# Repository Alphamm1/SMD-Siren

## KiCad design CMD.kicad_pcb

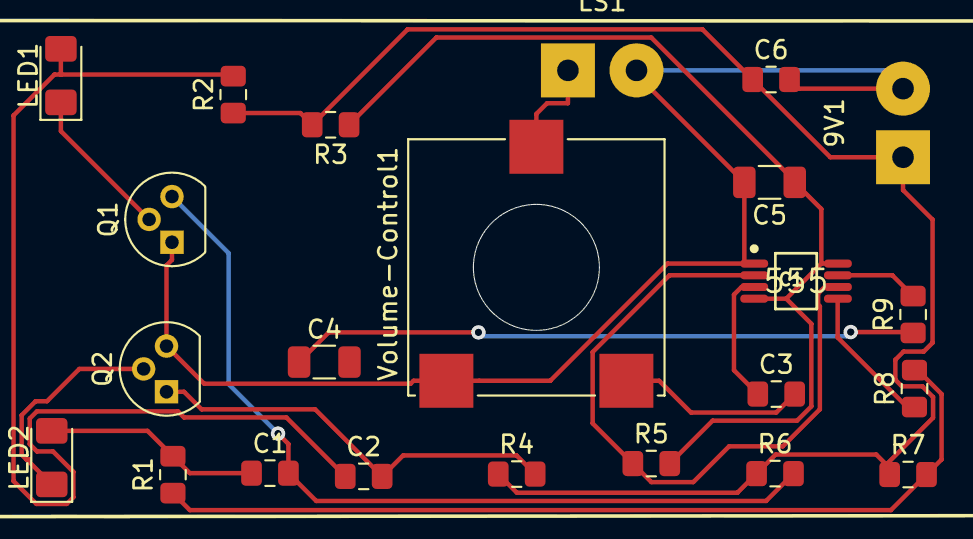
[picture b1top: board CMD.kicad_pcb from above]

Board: 2 copper layers, 23 parts (0 on the bottom side), 17 nets.

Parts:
9V1: Battery; SolderWirePad_1x02_P3.81mm_Drill1.2mm
C1, C2: CP1; C_0805_2012Metric_Pad1.15x1.40mm_HandSolder
C3: 10uF; C_0805_2012Metric_Pad1.15x1.40mm_HandSolder
C4, C5: 0.02uF; C_1206_3216Metric
C6: 100uF; C_0805_2012Metric_Pad1.15x1.40mm_HandSolder
IC1: 555; Texas_Instruments-LMC555CMM_NOPB-Level_A
LED1, LED2: LED_ALT; D_1206_3216Metric_Pad1.42x1.75mm_HandSolder
LS1: Speaker; SolderWirePad_1x02_P3.81mm_Drill1.2mm
Q1, Q2: Q_NPN_BCE; TO-92
R1, R7: 470; R_0805_2012Metric_Pad1.15x1.40mm_HandSolder
R2: 1K; R_0805_2012Metric_Pad1.15x1.40mm_HandSolder
R3: 68; R_0805_2012Metric_Pad1.15x1.40mm_HandSolder
R4, R6: 22K; R_0805_2012Metric_Pad1.15x1.40mm_HandSolder
R5: 47K; R_0805_2012Metric_Pad1.15x1.40mm_HandSolder
R8, R9: 10K; R_0805_2012Metric_Pad1.15x1.40mm_HandSolder
Volume-Control1: 200; Potentiometer_ACP_CA14-VSMD_Vertical_Hole

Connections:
GNDD: 9V1.2, C5.2, C6.2, IC1.1, LS1.2, Q1.1, Q2.3, Volume-Control1.3
unnamed: 9V1.1, C6.1, R2.1, R3.2, R4.1, R6.1, R7.1
unnamed: C1.1, LED2.2, R1.2
unnamed: C1.2, Q1.3, R6.2
unnamed: C2.1, LED1.2, R2.2
unnamed: C2.2, Q2.1, R4.2
unnamed: C3.1, IC1.3
unnamed: C3.2, Volume-Control1.1
unnamed: C4.1, R9.1
unnamed: C5.1, IC1.4, IC1.8, R3.1, R5.2
unnamed: IC1.2, IC1.6, R5.1
unnamed: IC1.5, R8.1
unnamed: IC1.7, R9.2
unnamed: LED1.1, Q1.2
unnamed: LED2.1, Q2.2
unnamed: LS1.1, Volume-Control1.2
unnamed: R1.1, R7.2, R8.2

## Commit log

2022-10-19 first project
2022-10-20 Added compoenents and made connections.
2022-10-20 Added foorprints, 3 footprints remaining.
2022-10-20 Started layout.
2022-10-26 Finished routing.
2022-10-30 Replaced EARTH > GND, Replaced 555 Footprint.
